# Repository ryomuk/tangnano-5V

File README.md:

# tangnano-5V
5V tolerant interface for Tang Nano 20K and 9K

This document is written mostly in Japanese. If necessary, please use a translation service such as DeepL (I recommend this) or Google.

# 概要
Tang Nanoを5V系の回路に接続するためのインターフェースです．昔のCPU用のメモリシステムやI/OをTang Nanoに実装することを主目的に作成しました。
Tang Nano 20K用と9K用の2種類があります．(私は主に20K用を使用しており，9K用はクセがあるのであまり使用実績が無いです．)

# Tang Nano 20K 版(rev.1.1a)
## 機能
- Tang Nanoの20KのGPIO(全34本)を，SN74CB3T3245(レベルシフタ搭載バススイッチ)を介して5V系(TTL, CMOS)に接続します．
- バッファではなくスイッチで行なっているため，特に信号方向を意識することなく双方向接続が可能，信号の伝達遅延は0.25ns以下です．

## 原理
- 5V→3.3VはSN74CB3T3245によって5V系から3.3V系にレベル変換されます．
- 3.3V→5Vはレベル変換は行なわれず，3.3V系の信号が出力されますが，5VTTLの閾値は1.5V，5VCMOSの閾値は2.5Vなので問題無いということのようです．

## 動作の確認状況
- 27MHzのシステムクロックが全GPIOで5V系に出力できることを確認しました．(75番ピンについては下記参照)
- 5V系→3.3V系: 5Vの入力信号に対し，出力が3.3Vになることを確認しました．
- 3.3V系→5V系: 3.3Vの入力信号に対し，出力が3.3Vになることを確認しました．
- データシートによると遅延はmax 0.25nsで，手元のオシロでは測定限界以下でした．

## Tang Nano 20Kの75番ピンについて
- Tang Nano 20K(v3921)の75番ピンは，C51(100nF)でGNDに接続されているため，そのままだと低速(数十KHz)でしか動作しません．他のピンと同様に使用するためにはC51を外す必要があります．低速動作で構わないのであれば気にしなくていいです．
- 最新の回路図v3921(Date:2023-07-11, ファイルの日付2023-11-08)ではC51がNCになっているようです。2024年3月に購入したものがC51未実装だったという情報がありました。(2024/4/15)
- R22(10K)でGNDにプルダウンされているので、外部でプルアップすると誤動作の原因になります。

### 75番ピン以外に関するメモ
TangNano20K、pin75以外にも若干癖のあるpinがあるのでメモしておきます。
- pin15～20は510RでLEDに継がっていて入力に使うとIIL=約3.0mA。
- pin52～53は2.2Kで5VとFETに継がっててIIL=約4.4mA。
- pin26は5.1KでGND、IIH=0.6mA。
- その他のほとんどのピンはだいたいIIL=0.9mA程度、IIH=0.1mA以下。

## BOM
|Reference          |Qty| Value          |Size |Memo |
|-------------------|---|----------------|-----|-----|
|C1, C2, C3, C4, C5 |5	|0.1uF	         |1608(mm)(0603(inch))| |
|J1, J2	            |2	|pin socket      |1x20 |for Tang Nano 20K|
|J3, J4             |2	|pin header      |1x20 |for 5V GPIO|
|U1, U2, U3, U4, U5 |5	|SN74CB3T3245PW  |TSSOP| |

## 画像

# 応用例
- いろいろなCPUのメモリシステム，UARTを構築した応用例です．CPUをFPGAでエミュレートするのではなく、本物のCPUを動かすことを目的にしています。
- 勉強のために作った習作なのでかなり荒削りでいろいろと不備やバグがあると思いますがご容赦下さい。
- 各CPUで共通に使用しているUARTモジュールは適当に作ったために時々不具合が見つかってバグ修正しています．旧版との互換性は確認していないので，CPUによっては旧版のままになっています．最新版は別フォルダ [applications/uart/](applications/uart/) に置いてありますので，必要であればコピーしてご使用下さい．
- ターミナルソフトの通信遅延はCPUの速度や通信速度にあわせて適宜設定して下さい。(例: 10ms/文字, 100ms/行)

## TangNanoZ80MEM [applications/TangNanoZ80MEM](applications/TangNanoZ80MEM)
- Z80用のメモリシステムとクロック，UARTです．
- 関連ブログ [Z80をオーバークロックしてみる](https://blog.goo.ne.jp/tk-80/e/6de3708450bac79c2c1cef7728d0c877)
  
## TangNanoZ80MEM-CPM [applications/TangNanoZ80MEM-CPM](applications/TangNanoZ80MEM-CPM)
- TangNanoZ80MEMにfloppy/hard diskエミュレータを追加してCP/Mを動作させる試みです．

## TangNano6809MEM [applications/TangNano6809MEM](applications/TangNano6809MEM)
- MC6809用のメモリシステムとクロック，UARTです．
- [電脳伝説さんのSBC6809](https://vintagechips.wordpress.com/2017/12/05/sbc6809%E3%83%AB%E3%83%BC%E3%82%BA%E3%82%AD%E3%83%83%E3%83%88/)のdatapackに入っているBASIC9がバイナリそのままで動きます．

## TangNano8070MEM [applications/TangNano8070MEM](applications/TangNano8070MEM)
- INS8070N(SC/MP III)用のメモリシステム，クロック，UARTです．
- [ElectrelicさんのUniversal Monitor](https://electrelic.com/electrelic/node/1317)が，UARTのハンドシェイク部分を微修正して動きました．

## TangNano8008MEM [applications/TangNano8008MEM](applications/TangNano8008MEM)
- Intel 8008用のメモリシステム，クロック，UARTです．
- [SCELBAL (SCELBI Basic)](https://www.willegal.net/scelbi/scelbal.html)が動きました．
- [VTL-4004](https://github.com/ryomuk/VTL4004)を8008用に書き直したVTL-8008が動きました

## TangNano8080MEM [applications/TangNano8080MEM](applications/TangNano8080MEM)
- Intel 8080用メモリシステム，クロック，UART，diskエミュレータです．
- Z80MEM-CPMと同じdiskイメージを使用してCP/Mが起動します．

## TangNanoDCJ11MEM [ryomuk/TangNanoDCJ11MEM](https://github.com/ryomuk/TangNanoDCJ11MEM)

- DEC DCJ11 (PDP-11の命令セットを持つCPU)のメモリシステムとUARTです。
- 詳細は別リポジトリ[TangNanoDCJ11MEM](https://github.com/ryomuk/TangNanoDCJ11MEM) にあります。

# Tang Nano 9K 版(rev.3.0)[hardware/9k](hardware/9k)
- Tang Nanoの9K用のインターフェースです．あまりメンテナナスされていません．

# その他
## UARTモジュールについて [applications/uart/](applications/uart/)
- 各応用例の通信部分はSipeedのサンプル( https://github.com/sipeed/TangNano-20K-example )をベースにして独自に書き替えたものを使っています．CPU速度と通信速度によっては不安定だったりすることがあり，時々書き直してます．旧版との互換性を全部確認するのは面倒なので最新版は別のフォルダに入れることにしました．

## 参考文献，データシート等
- [SN74CB3T3245 Data sheet](https://www.ti.com/lit/ds/symlink/sn74cb3t3245.pdf)
- [Application Note CBT-C, CB3T, and CB3Q Signal-Switch Families](https://www.ti.com/lit/an/scda008c/scda008c.pdf)
- [Logic Guide, Texas Instruments](https://www.ti.com/lit/sg/sdyu001ab/sdyu001ab.pdf)
- [ロジック・ガイド(日本語版), Texas Instruments](https://www.tij.co.jp/jp/lit/sg/jajt217/jajt217.pdf)
- [5V系・3.3V系信号レベル変換, cepstrum](https://www.cepstrum.co.jp/hobby/5v33v/5v33v.html)

## 更新履歴
- 2023/06/16: 初版公開 (Tang Nano 20K用 rev.1.1)
- 2023/06/25: 応用例にTangNanoZ80MEMを追加
- 2023/06/26: TangNanoZ80MEMのピン配置を変更．(rev1.0→rev.1.1)
- 2023/06/28: TangNanoZ80MEMの uart.vを更新．
- 2023/07/06: TangNanoZ80MEMを修正．27MHz(Vcc=5.0V), 33MHz(Vcc=6.0V)で動作．
- 2023/07/11: Tang Nano 20K用 rev.1.1→rev.1.1a (差分はシルクの修正のみ)
- 2023/07/11: Tang Nano 9K用 rev.2.0公開 (若干問題あり)
- 2023/07/15: README.md用の画像を1.1aにアップデート
- 2023/07/19: 応用例にTangNano6809MEMを追加
- 2023/07/20: tn20k5v rev1.1aの実物作成，動作確認OK．写真掲載．
- 2023/07/23: 応用例にTangNano8070MEMを追加．
- 2024/04/07: uart.vのバグ修正．(tx_ready関連)
- 2024/04/11: TangNano6809MEMに関する注意事項記載
- 2024/04/12: uart.vの最新版格納用のフォルダ applications/uart を作成
- 2024/04/13: applications/uart/uart.v 更新
- 2024/04/14: README修正(応用例に関するエクスキューズを追記)
- 2024/04/15: README修正(6809、R1の除去について, TangNano20Kのピンに関するメモ)
- 2024/04/17: TangNanoZ80MEM: top.v修正(writeのバグ, RGBLED, UART_CTRL)
- 2024/04/17: TangNanoZ80MEM: rom/rom.unimon339.v 追加
- 2024/04/19: TangNanoZ80MEM: rom/bin2v.pl修正, romファイルの余計な0フィルを削除
- 2024/04/21: Tang Nano 9K用 rev.3.0公開
- 2024/04/27: TangNanoZ80MEM: UARTの送信タイミング変更
- 2024/05/07: applications/uart/にuart.v.20240507 追加
- 2024/06/21: applications/uart/にuart.v.20240621 追加
- 2024/06/21: rx_clear, tx_sendのロジックについてREADMEに追記
- 2024/07/23: READMEを階層化
- 2024/07/23: TangNanoZ80MEM-CPM 公開
- 2024/08/05: TangNano8008MEM 公開
- 2024/08/18: TangNano8008MEM用のsoftwareにVTL-8008を追加
- 2024/08/28: TangNano8008MEMにPCB rev1.0を追加
- 2024/09/08: TangNano8080MEM 公開
- 2024/09/13: TangNano8080MEM 修正 (memory writeタイミング修正, 3MHz対応)

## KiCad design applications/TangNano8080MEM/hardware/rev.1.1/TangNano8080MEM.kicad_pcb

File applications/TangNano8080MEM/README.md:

# TangNano8080MEM

## 概要
- Intel 8080用のメモリシステム，クロック，UART，diskエミュレータです．
- Universal Monitor や CP/Mが動きます．

## PCB rev.1.1
- 回路図，ガーバーファイル等は[hardware/rev.1.1](hardware/rev.1.1/)にあります．
### BOM
|Reference          |Qty| Value          |Memo |
|-------------------|---|----------------|-----|
|C1                 |1  |2.2uF           |     |
|C2,C6              |2  |1uF             |     |
|C3,C4              |2  |10uF            |     |
|C5,C7,C8           |3  |0.1uF           |     |
|D1,D2              |2  | LED            |任意     |
|J1                 |1  | DIP-40 Socket or 20x1 Pin frame x2  |TangNano5V用|
|J2,J3              |2  |Conn_01x20      |任意(観測用)|
|PS1                |1  |MAU104          |5V→12V用DCDC,  https://akizukidenshi.com/catalog/g/g104132/ |
|PS2                |1  |TJ7660          |5V→-5V用, https://akizukidenshi.com/catalog/g/g112017/|
|R1                 |1  | 10k             |     |
|R2,R3              |2  | 1k〜100k(適宜)     | 値はLEDにあわせて任意|
|R4,R5              |2  | 47     | クロック用ダンピング抵抗|
|RN1                |1  | 4.7k x8       |データバスプルアップ     |
|RN2                |1  | 100k x4       |制御信号プルアップ       |
|U1                 |1  | MIC4427 |  クロックドライバ|
|U2                 |1  | 40pin ZIFソケット |  8080用|

- RN2は当初10KΩにしていたのですが，TangNano20Kのpin75はB616_BOOTに継がっていて，起動時にUSBを検出してくれなくなってしまうので100kΩに変更しました．[TangNano6809MEM](../TangNano6809MEM)で起きていたのと同様の問題でした．

## FPGAに実装したもの
- [TangNanoZ80MEM-CPM](../TangNanoZ80MEM-CPM/)をベースにして，2相クロック，8228相当の制御信号の変換を追加しました．

## クロックの設定
top.v で下記の1つを選択して下さい．
```
// select one of the following CLK frequency
//`define  CLK_3MHz     // 3.0MHz(333ns)
`define  CLK_2MHz   // 2.077MHz( 481ns)
//`define  CLK_1MHz   // 1.038MHz( 963ns)
//`define  CLK_500kHz // 519.2KHz(1930ns)
```

## ROMの選択
- top.v で下記の1つを選択して下さい．
```
// select one of the following 2 applications
`define USE_CPM
//`define USE_UNIMON

```
このオプションで，rom.vでincludeするファイル，UART用レジスタのビットフィールドを切り替えています．

## CP/Mの起動方法
- [TangNanoZ80-CPM](../TangNanoZ80MEM-CPM/)と同じ手順で作成したdiskイメージで起動できます．

## 動作確認状況
- 下記CPUで動作CP/Mが起動し，BASICでASCIIART.BASが完走しました．

#### Intel C8080A

#### Intel P8080A-1 (3MHz)

#### NEC uPD8080A

#### NEC uPD8080AF

#### NEC uPD8080AFC-1 (3MHz)

#### NEC uPD753(+変換基板)

#### 三菱M58710S(8080A)

#### AMD AM9080ADC(C8080A)

#### AMD AM9080ADCB

#### NS INS8080AN

#### TI TMS8080ANL

## 既知の問題
- ~~下記CPUで動作しないので原因調査中です．~~
  - ~~NS INS8080AN, TI TMS8080ANL~~
  - メモリ書き込みのタイミングを修正して解決しました．

## 参考にした先行事例，関連サイト等
- [satoshiokue/MEZ8080](https://github.com/satoshiokue/MEZ8080)
- [satoshiokue/EMUZ80-8080](https://github.com/satoshiokue/EMUZ80-8080)
- [Gazelle8087/EMUZ80-8080G](https://github.com/Gazelle8087/EMUZ80-8080G)
- [電脳伝説/SBC8080](https://vintagechips.wordpress.com/2018/06/24/sbc8080-cpu%E3%83%AB%E3%83%BC%E3%82%BA%E3%82%AD%E3%83%83%E3%83%88/)
- [Electrelic/Universal Monitor](https://electrelic.com/electrelic/node/1317)

## 更新履歴
- 2024/09/08: 初版公開
- 2024/09/13: メモリライトタイミング修正，3MHz対応

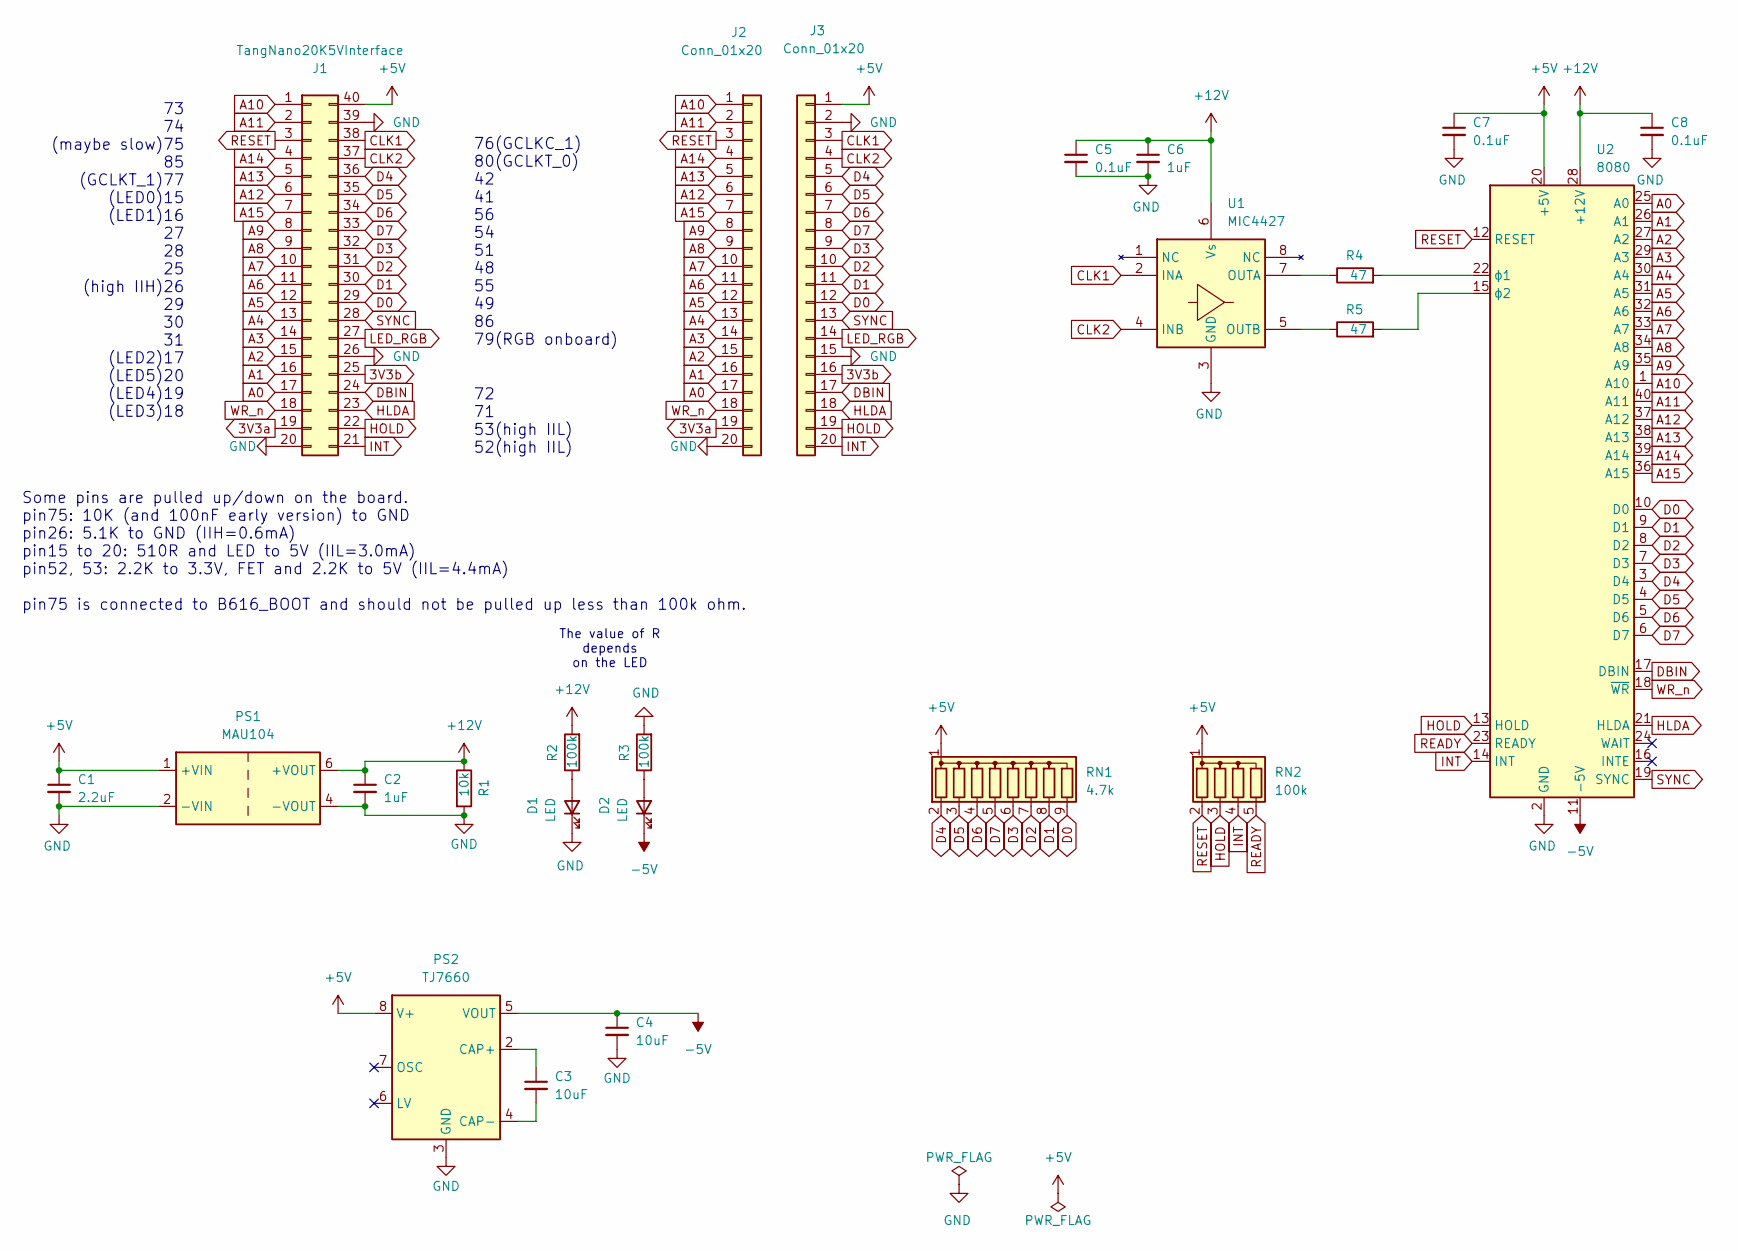
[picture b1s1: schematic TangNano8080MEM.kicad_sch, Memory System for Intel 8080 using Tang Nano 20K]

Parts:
C1: 2.2uF; C_Disc_D4.7mm_W2.5mm_P5.00mm
C2, C6: 1uF; C_Disc_D4.7mm_W2.5mm_P5.00mm
C3, C4: 10uF; C_Disc_D4.7mm_W2.5mm_P5.00mm
C5, C7, C8: 0.1uF; C_Disc_D5.0mm_W2.5mm_P2.50mm
D1, D2: LED; LED_D3.0mm
J1: TangNano20K5VInterface; DIP-40_W15.24mm_Socket
J2, J3: Conn_01x20; PinSocket_1x20_P2.54mm_Vertical
PS1: MAU104; SIP-6_without_3_5pin_for_DCDC_MAU
PS2: TJ7660; DIP-8_W7.62mm
R1: 10k; R_Axial_DIN0207_L6.3mm_D2.5mm_P7.62mm_Horizontal
R2, R3: 100k; R_Axial_DIN0207_L6.3mm_D2.5mm_P7.62mm_Horizontal
R4, R5: 47; R_Axial_DIN0207_L6.3mm_D2.5mm_P7.62mm_Horizontal
RN1: 4.7k; R_Array_SIP9
RN2: 100k; R_Array_SIP5
U1: MIC4427; DIP-8_W7.62mm
U2: 8080; DIP_Socket-40_W11.9_W12.7_W15.24_W17.78_W18.5_3M_240-1280-0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

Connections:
3V3a: J1.19, J2.19
3V3b: J1.25, J3.16
+5V: C1.1, C7.1, J1.40, J3.1, PS1.1 (+VIN), PS2.8 (V+), RN1.1 (common), RN2.1 (common), U2.20 (+5V)
+12V: C2.1, C5.1, C6.1, C8.1, PS1.6 (+VOUT), R1.1, R2.2, U1.6 (Vs), U2.28 (+12V)
-5V: C4.1, D2.1 (K), PS2.5 (VOUT), U2.11 (-5V)
A0: J1.17, J2.17, U2.25 (A0)
A1: J1.16, J2.16, U2.26 (A1)
A2: J1.15, J2.15, U2.27 (A2)
A3: J1.14, J2.14, U2.29 (A3)
A4: J1.13, J2.13, U2.30 (A4)
A5: J1.12, J2.12, U2.31 (A5)
A6: J1.11, J2.11, U2.32 (A6)
A7: J1.10, J2.10, U2.33 (A7)
A8: J1.9, J2.9, U2.34 (A8)
A9: J1.8, J2.8, U2.35 (A9)
A10: J1.1, J2.1, U2.1 (A10)
A11: J1.2, J2.2, U2.40 (A11)
A12: J1.6, J2.6, U2.37 (A12)
A13: J1.5, J2.5, U2.38 (A13)
A14: J1.4, J2.4, U2.39 (A14)
A15: J1.7, J2.7, U2.36 (A15)
CLK1: J1.38, J3.3, U1.2 (INA)
CLK2: J1.37, J3.4, U1.4 (INB)
D0: J1.29, J3.12, RN1.9 (R8), U2.10 (D0)
D1: J1.30, J3.11, RN1.8 (R7), U2.9 (D1)
D2: J1.31, J3.10, RN1.7 (R6), U2.8 (D2)
D3: J1.32, J3.9, RN1.6 (R5), U2.7 (D3)
D4: J1.36, J3.5, RN1.2 (R1), U2.3 (D4)
D5: J1.35, J3.6, RN1.3 (R2), U2.4 (D5)
D6: J1.34, J3.7, RN1.4 (R3), U2.5 (D6)
D7: J1.33, J3.8, RN1.5 (R4), U2.6 (D7)
DBIN: J1.24, J3.17, U2.17 (DBIN)
GND: C1.2, C2.2, C4.2, C5.2, C6.2, C7.2, C8.2, D1.1 (K), J1.20, J1.26, J1.39, J2.20, J3.2, J3.15, PS1.2 (-VIN), PS1.4 (-VOUT), PS2.3 (GND), R1.2, R3.2, U1.3 (GND), U2.2 (GND)
HLDA: J1.23, J3.18, U2.21 (HLDA)
HOLD: J1.22, J3.19, RN2.3 (R2), U2.13 (HOLD)
INT: J1.21, J3.20, RN2.4 (R3), U2.14 (INT)
LED_RGB: J1.27, J3.14
unnamed: D1.2 (A), R2.1
unnamed: D2.2 (A), R3.1
unnamed: C3.1, PS2.2 (CAP+)
unnamed: C3.2, PS2.4 (CAP-)
unnamed: R4.1, U1.7 (OUTA)
unnamed: R5.1, U1.5 (OUTB)
unnamed: R4.2, U2.22 (ϕ1)
unnamed: R5.2, U2.15 (ϕ2)
READY: RN2.5 (R4), U2.23 (READY)
RESET: J1.3, J2.3, RN2.2 (R1), U2.12 (RESET)
SYNC: J1.28, J3.13, U2.19 (SYNC)
WR_n: J1.18, J2.18, U2.18 (~WR)

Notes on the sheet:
72 71 53(high IIL) 52(high IIL)
73 74 (maybe slow)75 85 (GCLKT_1)77 (LED0)15 (LED1)16 27 28 25 (high IIH)26 29 30 31 (LED2)17 (LED5)20 (LED4)19 (LED3)18
76(GCLKC_1) 80(GCLKT_0) 42 41 56 54 51 48 55 49 86 79(RGB onboard)
Some pins are pulled up/down on the board. pin75: 10K (and 100nF early version) to GND pin26: 5.1K to GND (IIH=0.6mA) pin15 to 20: 510R and LED to 5V (IIL=3.0mA) pin52, 53: 2.2K to 3.3V, FET and 2.2K to 5V (IIL=4.4mA) pin75 is connected to B616_BOOT and should not be pulled up less than 100k ohm.
The value of R depends on the LED

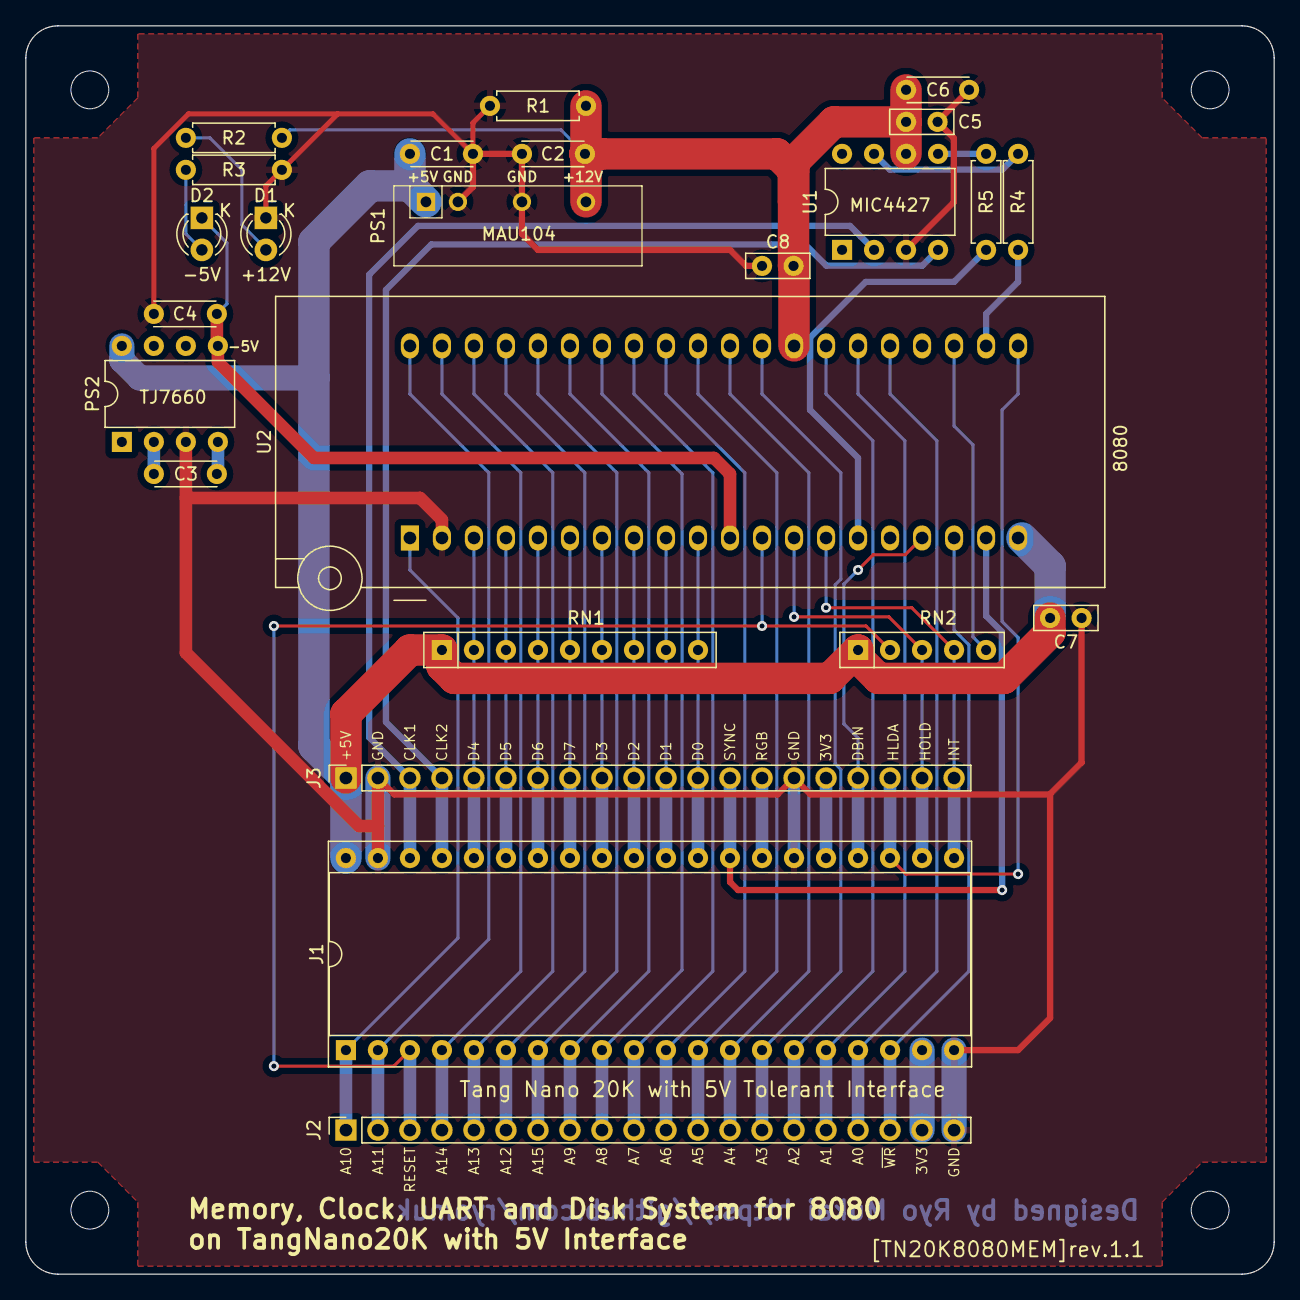
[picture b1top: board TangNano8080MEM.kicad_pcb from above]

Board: 2 copper layers, 99.1 x 99.1 mm, 24 parts (0 on the bottom side), 49 nets.

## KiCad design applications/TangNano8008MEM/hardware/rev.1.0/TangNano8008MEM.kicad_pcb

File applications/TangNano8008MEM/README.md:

# TangNano8008MEM
## 概要
- Intel 8008用のメモリシステム，クロック，UARTです．

## PCB rev.1.0

- 回路図やガーバーファイルは[hardware/rev.1.0](hardware/rev.1.0/)にあります．
- users manualには入出力はTTLレベルと書いてありますが，波形を観測したところ8008の出力はマイナス電位にもなるようでした．
  - バス(D0〜7)には外付けでクランプダイオードを回路に入れていますが，SN74CB3T3245にはクランプダイオードが内蔵されているので無くても動きます．
  - SYNC, S0〜2は1KΩの抵抗だけ入れてSN74CB3T3245内蔵のクランプダイオードに任せています．
### BOM
|Reference          |Qty| Value          |Memo |
|-------------------|---|----------------|-----|
|C1                 |1  |2.2uF           |     |
|C2                 |1  |1uF             |     |
|D1-D8              |8  |1N4148          |     |
|D9                 |1  | LED      |任意     |
|J1                 |1  | DIP-40 Socket or 20x1 Pin frame x2  |TangNano5V用|
|PS1                |1  |MAU103          |5V→9V用DCDC,  https://akizukidenshi.com/catalog/g/g112176/ |
|R1-R5              |5  | 1k             |     |
|R6                 |1  | 100k(適宜)     | 値はLEDにあわせて任意|
|RN1, RN3           |2  | 4.7k x8       |     |
|RN2                |1  | 1k x4          |     |
|U1                 |1  | 18pin ZIFソケット |  intel8008用|

## FPGAに実装したもの
- プロジェクトは[TangNano8008MEM_project](TangNano8008MEM_project)です．
- 16KBメモリ (8008のアドレス空間は14bitなのでフル実装です．)
- UART(TXバッファ付き)
- 割り込み機能
- 8008にはRESETが無いので，下記でRESET相当のことを実装しました．
  - SW1: バスにHALTを出力してSTOPさせ，INTERRUPT信号をアサートし，バスにRST0命令を挿入．(power-up時も同様)
  - SW2: INTERRUPT信号をアサートし，バスにRST0命令を挿入

## ソフトウェアについて
### VTL-8008 ([software/VTL8008](software/VTL8008))
- 以前，4004用に書いた[VTL-4004](https://github.com/ryomuk/VTL4004)を8008用に書き直してみました．仕様はVTL-4004 ver2.0と同じです．面倒なので行の編集機能が実装していません．

### echo back test ([software/echo](software/echo))
- UARTの入出力テスト用プログラムです．
- polling版と割り込み版はecho.asmの下記2行と，top.vのdefineで切り替えます．
```
echo.asm
;;; uncomment this for polling
;;  	CAL GETCH
;;  	CAL PUTCH

top.v
//`define USE_RX_INTERRUPT
```

### SCELBAL (SCELBI Basic) ([software/sc1](software/sc1))
- Twitterで[SCELBAL (SCELBI Basic)](https://www.willegal.net/scelbi/scelbal.html)なるものが存在することを教えてもらったので試してみることにしました．

#### SCELBI Basicのバイナリ作成方法等
- [ASL(The Macroassembler AS)](http://john.ccac.rwth-aachen.de:8000/as/), Perlをインストールして下さい．私はWindowsのCygwin環境で使っています．
- ASLで，radix 8とすれば良いようだったのですが，その場合に10進数をどう表記するかわからなかったので，radixは10のままで8進数にQを付けるスクリプトを書いて対処しました．その他の修正も全部スクリプト(conv.pl)で実施するようにしました．
- どうやら文字コードの8bit目が1のようで，コンソールの入出力は入出力ルーチンで対処すれば簡単だったのですが，アセンブラのプログラムの方も
```
DB "FOR"
```
を
```
DB 'F'+80H
DB 'O'+80H
DB 'R'+80H
```
のように展開する必要があるようなので変換しました．
- I/Oルーチン(CINP, CPRINT)を書く必要があったので user.asm に書きました．
  - 文字コードの8bit目が1であることへの対応．
  - どうやらCINPではecho処理も行う必要があるようでした．
- バイナリ作成手順は下記の通り．
```
cd TangNano8008MEM/software/sc1
wget https://www.willegal.net/scelbi/software/sc1.asm
cp sc1.asm sc1.asm.org
./conv.pl < sc1.asm.org > sc1.asm
make
./bin2v sc1.bin > rom.v
```
- Faster SCELBAL (2012) [sc1fast.asm](https://www.willegal.net/scelbi/software/sc1fast.asm) もconv.plで変換できました．
  - diffをとってみたらsc1.asmとの差分はほとんどありませんでした．
  - 構文解析処理を工夫して高速化しているようです．
  - mandelbrot.asmは10%ほど速くなりました．浮動小数点演算が支配項なので効果は限定的でした．

#### 実行サンプル
- お約束のASCIIART.BASを実行してみました．FOR文からGOTOで抜けるとエラーになるので微修正しました．
- 計測マクロがうまく動かず，正確な時間は測定できなかったのですが，クロッ
ク500kHzで約6時間40分で完走しました．

## ブレッドボード版

- 配線量が少なく，クロックも低速なのでブレッドボードで簡単に作れました．
 - ~~あまりに簡単に作れたので，基板を作るモチベーションが湧きません．~~
 - ブレッドボードを再利用するために基板を作りました．

## 関連情報
- [bitsavers /intel/MCS8](http://www.bitsavers.org/components/intel/MCS8/)
- [www.mars.dti.ne.jp/~mark08](http://www.mars.dti.ne.jp/~mark08/index.html) 8008に関する日本語の参考資料について網羅されています．
- [SCELBAL (SCELBI Basic)](https://www.willegal.net/scelbi/scelbal.html)
- [github.com/jim11662418/8008-SBC](https://github.com/jim11662418/8008-SBC)
- [The Macroassembler AS](http://john.ccac.rwth-aachen.de:8000/as/)

## 更新履歴
- 2024/08/05: 初版公開
- 2024/08/18: VTL-8008を追加
- 2024/08/28: KiCADファイルrev1.0をブレッドボード用からプリント基板用に変更

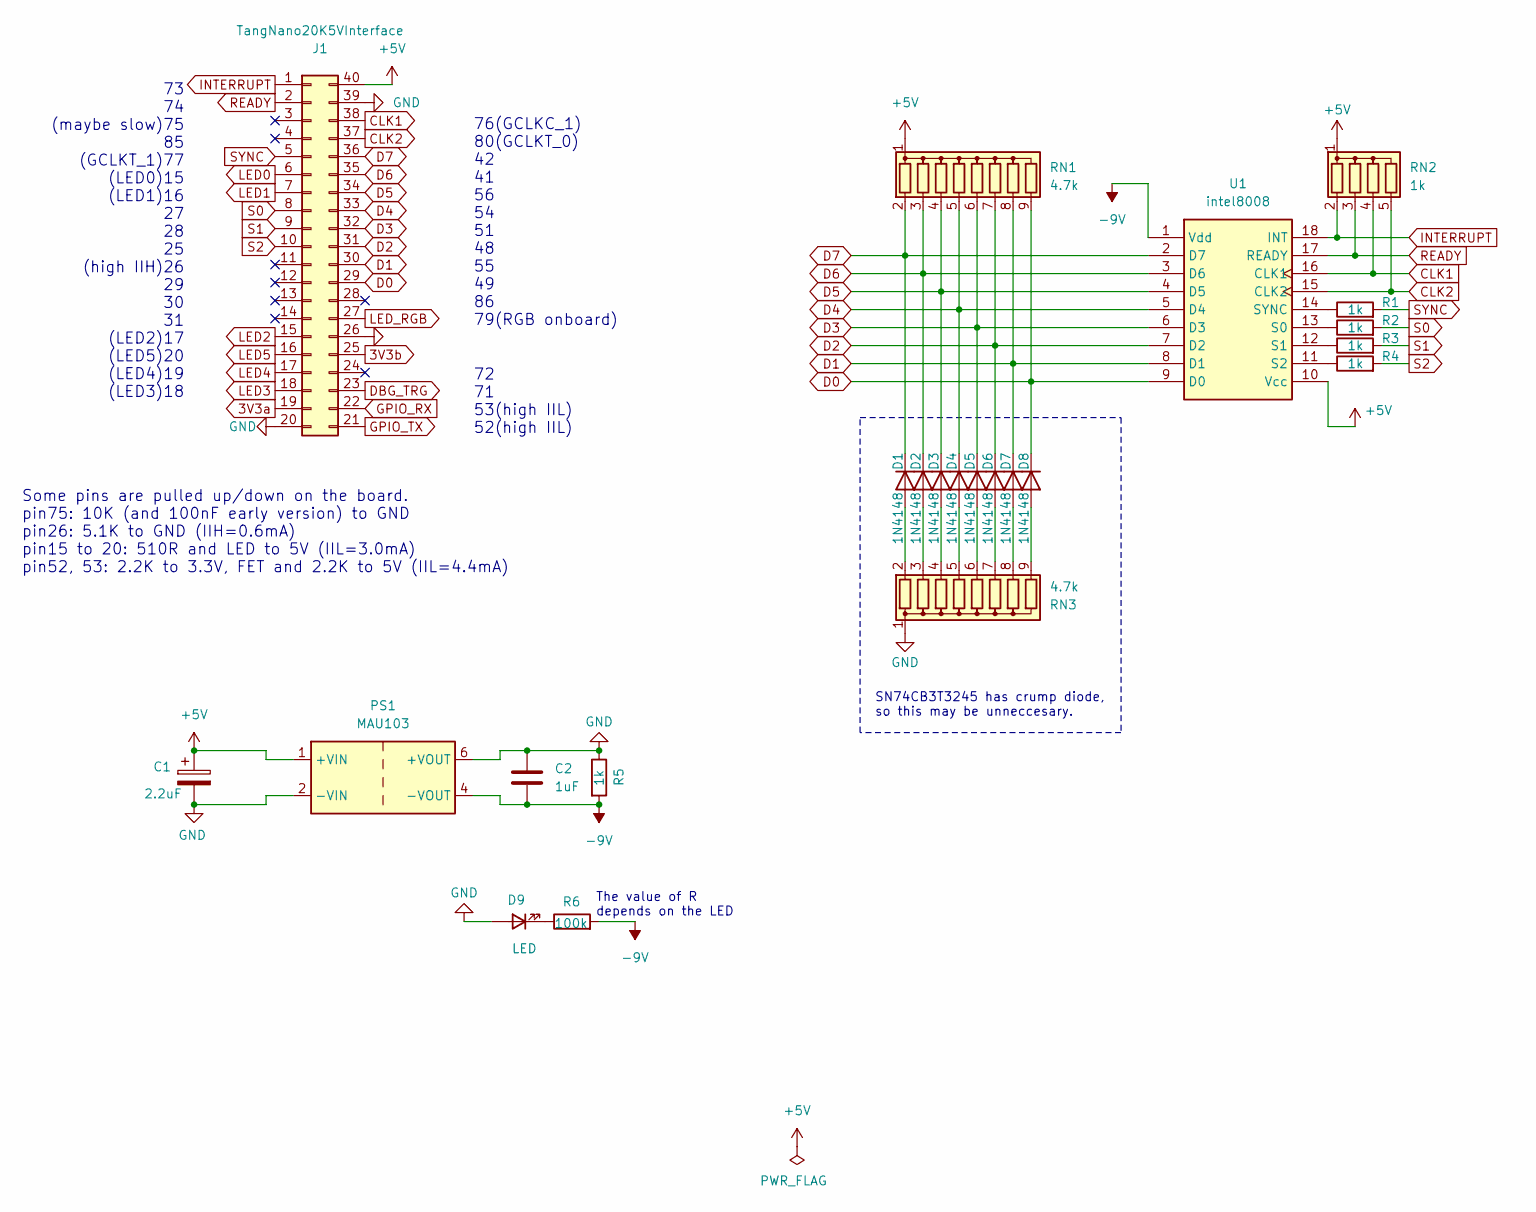
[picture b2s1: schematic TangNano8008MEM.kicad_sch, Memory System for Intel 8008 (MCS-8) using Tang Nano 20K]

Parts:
C1: 2.2uF; CP_Radial_D5.0mm_P2.00mm
C2: 1uF; C_Disc_D4.7mm_W2.5mm_P5.00mm
D1, D2, D3, D4, D5, D6, D7, D8: 1N4148; D_DO-35_SOD27_P2.54mm_Vertical_KathodeUp
D9: LED; LED_D3.0mm
J1: TangNano20K5VInterface; DIP-40_W15.24mm_Socket
PS1: MAU103; SIP-6_without_3_5pin_for_DCDC_MAU
R1, R2, R3, R4, R5: 1k; R_Axial_DIN0207_L6.3mm_D2.5mm_P7.62mm_Horizontal
R6: 100k; R_Axial_DIN0207_L6.3mm_D2.5mm_P7.62mm_Horizontal
RN1, RN3: 4.7k; R_Array_SIP9
RN2: 1k; R_Array_SIP5
U1: intel8008; DIP_Socket-18_W4.3_W5.08_W7.62_W10.16_W10.9_3M_218-3341-00-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

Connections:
3V3a: J1.19
3V3b: J1.25
+5V: C1.1, J1.40, PS1.1 (+VIN), RN1.1 (common), RN2.1 (common), U1.10 (Vcc)
-9V: C2.2, PS1.4 (-VOUT), R5.2, R6.2, U1.1 (Vdd)
CLK1: J1.38, RN2.4 (R3), U1.16 (CLK1)
CLK2: J1.37, RN2.5 (R4), U1.15 (CLK2)
D0: D8.1 (K), J1.29, RN1.9 (R8), U1.9 (D0)
D1: D7.1 (K), J1.30, RN1.8 (R7), U1.8 (D1)
D2: D6.1 (K), J1.31, RN1.7 (R6), U1.7 (D2)
D3: D5.1 (K), J1.32, RN1.6 (R5), U1.6 (D3)
D4: D4.1 (K), J1.33, RN1.5 (R4), U1.5 (D4)
D5: D3.1 (K), J1.34, RN1.4 (R3), U1.4 (D5)
D6: D2.1 (K), J1.35, RN1.3 (R2), U1.3 (D6)
D7: D1.1 (K), J1.36, RN1.2 (R1), U1.2 (D7)
DBG_TRG: J1.23
GND: C1.2, C2.1, D9.2 (A), J1.20, J1.26, J1.39, PS1.2 (-VIN), PS1.6 (+VOUT), R5.1, RN3.1 (common)
GPIO_RX: J1.22
GPIO_TX: J1.21
INTERRUPT: J1.1, RN2.2 (R1), U1.18 (INT)
LED0: J1.6
LED1: J1.7
LED2: J1.15
LED3: J1.18
LED4: J1.17
LED5: J1.16
LED_RGB: J1.27
unnamed: D1.2 (A), RN3.2 (R1)
unnamed: D2.2 (A), RN3.3 (R2)
unnamed: D3.2 (A), RN3.4 (R3)
unnamed: D4.2 (A), RN3.5 (R4)
unnamed: D5.2 (A), RN3.6 (R5)
unnamed: D6.2 (A), RN3.7 (R6)
unnamed: D7.2 (A), RN3.8 (R7)
unnamed: D8.2 (A), RN3.9 (R8)
unnamed: D9.1 (K), R6.1
unnamed: R2.1, U1.13 (S0)
unnamed: R3.1, U1.12 (S1)
unnamed: R4.1, U1.11 (S2)
unnamed: R1.1, U1.14 (SYNC)
READY: J1.2, RN2.3 (R2), U1.17 (READY)
S0: J1.8, R2.2
S1: J1.9, R3.2
S2: J1.10, R4.2
SYNC: J1.5, R1.2

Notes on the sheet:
SN74CB3T3245 has crump diode, so this may be unneccesary.
72 71 53(high IIL) 52(high IIL)
73 74 (maybe slow)75 85 (GCLKT_1)77 (LED0)15 (LED1)16 27 28 25 (high IIH)26 29 30 31 (LED2)17 (LED5)20 (LED4)19 (LED3)18
The value of R depends on the LED
76(GCLKC_1) 80(GCLKT_0) 42 41 56 54 51 48 55 49 86 79(RGB onboard)
Some pins are pulled up/down on the board. pin75: 10K (and 100nF early version) to GND pin26: 5.1K to GND (IIH=0.6mA) pin15 to 20: 510R and LED to 5V (IIL=3.0mA) pin52, 53: 2.2K to 3.3V, FET and 2.2K to 5V (IIL=4.4mA)

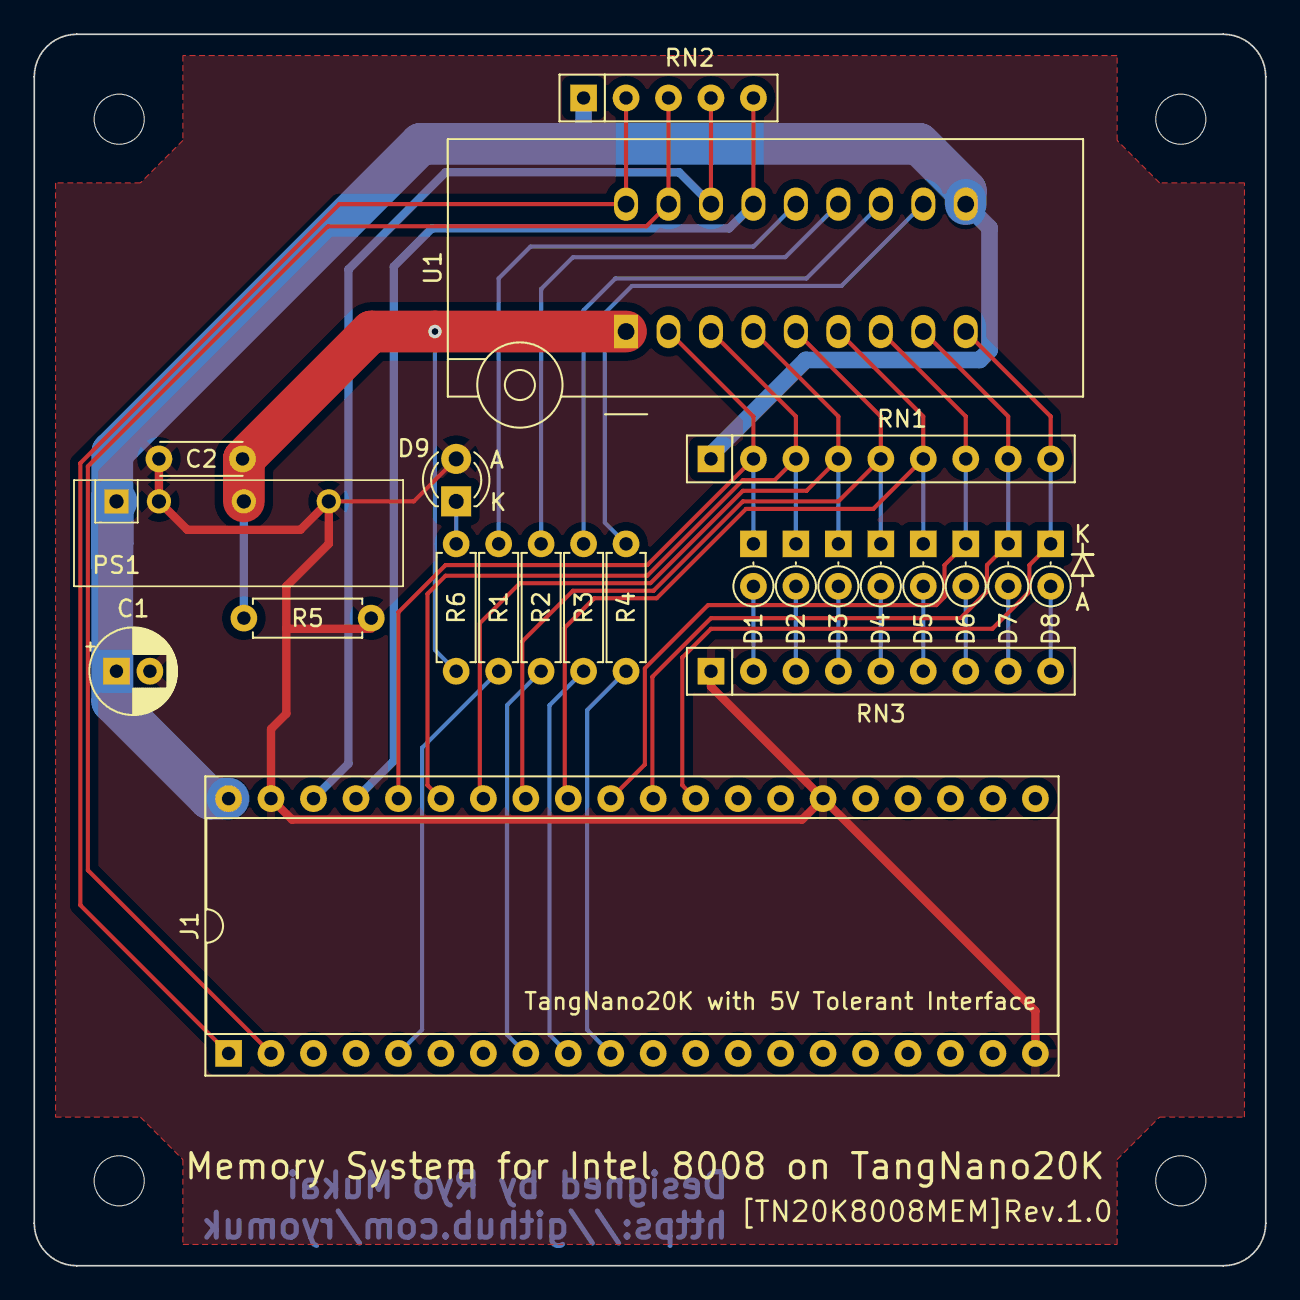
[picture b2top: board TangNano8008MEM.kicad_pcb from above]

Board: 2 copper layers, 73.7 x 73.7 mm, 23 parts (0 on the bottom side), 32 nets.

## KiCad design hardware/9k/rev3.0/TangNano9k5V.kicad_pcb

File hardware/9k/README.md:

# Tang Nano 9K 版(rev.3.0)
## rev2.0からの差分
- rev2.0(全バンクでTXS0108Eを使用)では、Pin68～75(HDMI用ピン)への入力で異常発振したり、USB接続が出来無くなったりする問題が発生していましたが、3.3Vバンクを20K版と同じ74CB3T3245に変更したところそれらの問題が解消しました。
  
## 機能
- Tang Nanoの9KのGPIO(全45本)を5V系(TTL, CMOS)に接続します．
- 信号方向を意識することなく双方向接続が可能です．
- Pin79〜86は1.8Vのバンク(BANK3)なのでTXS0108Eを用いて，1.8V←→(5V or 3.3V)の変換をします．その他のピンはCB3T3245を用いて3.3V←5V, 3.3V→3.3Vです．

## 動作の確認状況
- 27MHzのシステムクロックが全GPIOで5V系に出力できることを確認しました．
- 入力は単体試験(1ピンづつ)では期待通りの動きをしますが，入出力混在時に怪しい挙動を示しました．

### 見つかった問題点
- (pin63 & pin86) をそれ以外の全ピンに出力するというテストで出力がおかしくなることがある．おそらくBANK3(1.8V系)がなんらかの干渉をしている．
- pin68〜75は入出力とも若干歪む．

### 問題点を回避するためのガイドライン
- BANK3(1.8V系)は出力専用にする．
- HDMI用のピンは歪むので動作を確認しながら使う．

## BOM
|Reference            |Qty| Value          |Size |Memo |
|---------------------|---|----------------|-----|-----|
|C3,C4,C5,C6,C7,C8,C9 |7  |0.1uF	   |1608(mm)(0603(inch))|C1,C2は無し |
|J1                   |1  |pin header      |1x3 |BANK3 HI側の電圧選択用|
|J2,J3                |2  |pin socket      |1x24 |for TangNano9K|
|J4,J5                |2  |pin header      |1x24 |for 5V GPIO|
|PS1                  |1  |TLV71318        |SOT23-5| 1.8Vレギュレータ|
|U1                   |1  |TXS0108EPW      |TSSOP| |
|U2,U3,U4,U5,U6       |5  |SN74CB3T3245PW  |TSSOP| |

- C1,C2は.1.8Vレギュレータ用でしたが不要なので消した後にアノテーションし直すのを忘れて欠番になっています．

## 画像

## 応用例
## TangNanoZ80MEM_9K [applications/9K/TangNanoZ80MEM_9K](../../applications/9K/TangNanoZ80MEM_9K)

- 9K用インターフェースの動作確認用にブレッドボードで組んでみました．
- ~~とりあえず4.5MHzならたいていのピン配置で動きました．今のところ13.5MHzが限界．20K版ほど高速には動作しませんでした．~~
- ~~HDMIのコンデンサを外したら余計に動作しなくなったり，ピンアサインを変えるだけで動作しなくなったりするのでどこかにタイミング的な問題がありそうです．~~
- ~~MREQ_nはHDMIピンに継げた方が安定するので，MREQ_nでアドレスをラッチしているあたりが怪しそう．~~
- メモリライトのタイミングをWR_nではなくCLKでトリガーするようにしたら27MHzでも動くようになりました。ただし、HDMI端子のコンデンサ除去必須です。

## 更新履歴
- 2023/7/11: Tang Nano 9K用 rev.2.0公開 (若干問題あり)
- 2024/4/21: Tang Nano 9K用 rev.3.0公開

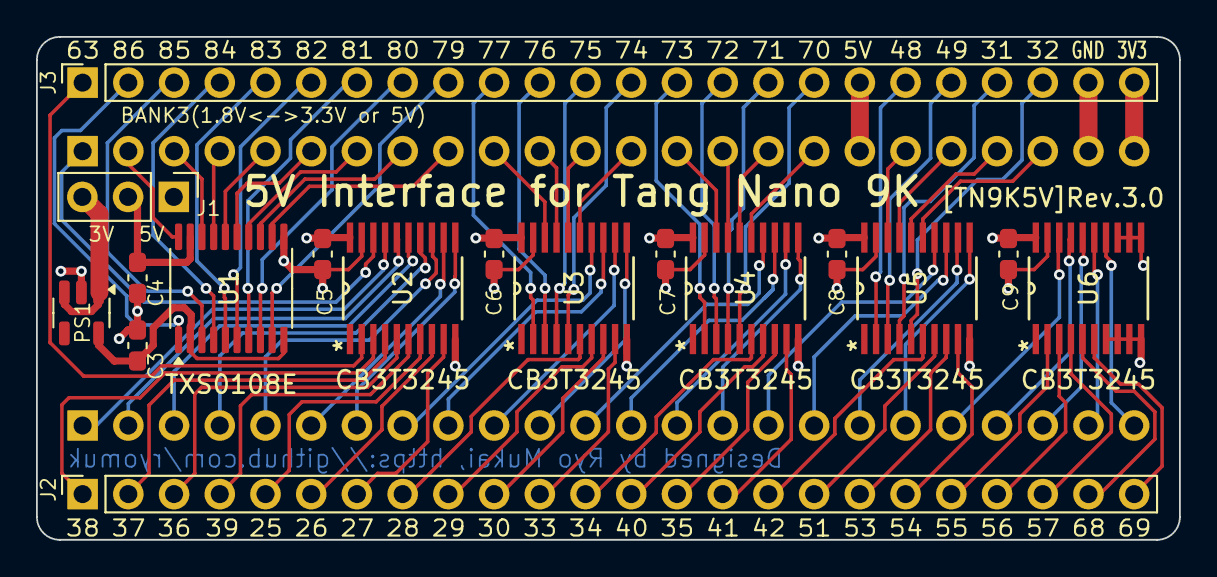
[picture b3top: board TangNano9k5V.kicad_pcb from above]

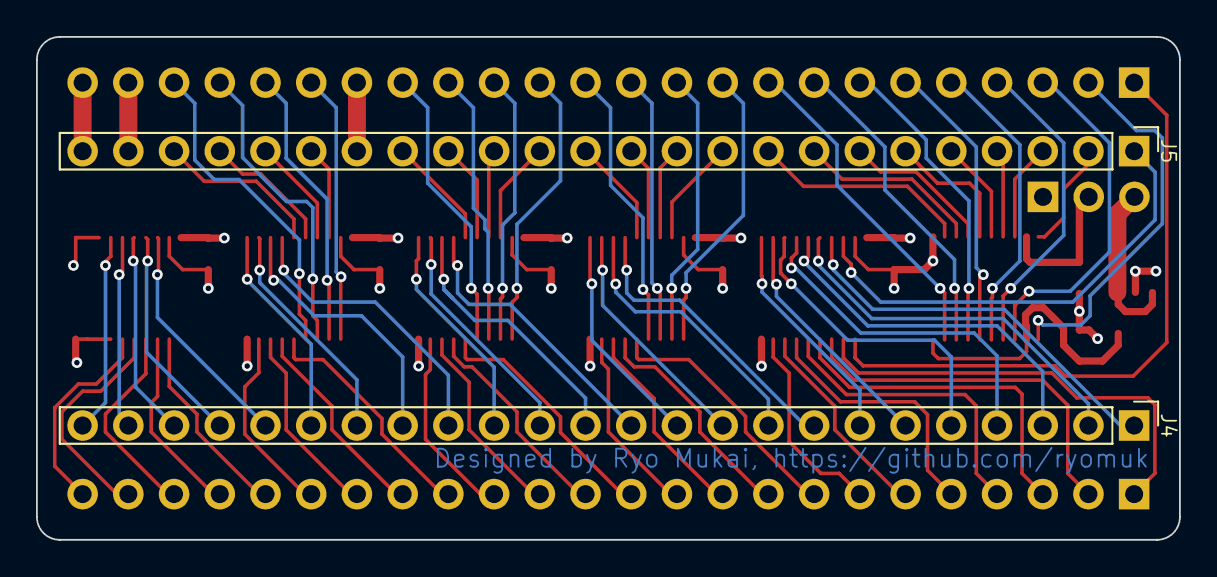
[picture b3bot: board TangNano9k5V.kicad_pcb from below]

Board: 4 copper layers, 63.5 x 27.9 mm, 19 parts (2 on the bottom side), 95 nets.

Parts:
C3, C4, C5, C6, C7, C8, C9: 0.1uF; C_0603_1608Metric_Pad1.08x0.95mm_HandSolder
J1: VCCB; PinHeader_1x03_P2.54mm_Vertical
J2, J3: Conn_01x24; PinSocket_1x24_P2.54mm_Vertical
J4, J5: Conn_01x24; PinHeader_1x24_P2.54mm_Vertical
PS1: TLV71318_SOT23-5; SOT-23-5
U1: TXS0108E; TSSOP-20_4.4x6.5mm_P0.65mm
U2, U3, U4, U5, U6: CB3T3245; PW20

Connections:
+1V8: C3.1, PS1.5 (OUT), U1.2 (VCCA), U1.10 (OE)
+3.3V: C5.1, C6.1, C7.1, C8.1, C9.1, J1.3, J3.24, J5.24, PS1.1 (IN), PS1.3 (EN), U2.20 (VCC), U3.20 (VCC), U4.20 (VCC), U5.20 (VCC), U6.20 (VCC)
+5V: J1.1, J3.18, J5.18
GND: C3.2, C4.2, C5.2, C6.2, C7.2, C8.2, C9.2, J3.23, J5.23, PS1.2 (GND), U1.11 (GND), U2.10 (GND), U2.19 (*OE), U3.10 (GND), U3.19 (*OE), U4.10 (GND), U4.19 (*OE), U5.10 (GND), U5.19 (*OE), U6.7 (A6), U6.8 (A7), U6.9 (A8), U6.10 (GND), U6.11 (B8), U6.12 (B7), U6.13 (B6), U6.19 (*OE)
unnamed: C4.1, J1.2, U1.19 (VCCB)
PIN25: J2.5, U2.7 (A6)
PIN25_H: J4.5, U2.13 (B6)
PIN26: J2.6, U2.8 (A7)
PIN26_H: J4.6, U2.12 (B7)
PIN27: J2.7, U2.9 (A8)
PIN27_H: J4.7, U2.11 (B8)
PIN28: J2.8, U3.6 (A5)
PIN28_H: J4.8, U3.14 (B5)
PIN29: J2.9, U3.7 (A6)
PIN29_H: J4.9, U3.13 (B6)
PIN30: J2.10, U3.8 (A7)
PIN30_H: J4.10, U3.12 (B7)
PIN31: J3.21, U5.4 (A3)
PIN31_H: J5.21, U5.16 (B3)
PIN32: J3.22, U5.5 (A4)
PIN32_H: J5.22, U5.15 (B4)
PIN33: J2.11, U3.9 (A8)
PIN33_H: J4.11, U3.11 (B8)
PIN34: J2.12, U4.6 (A5)
PIN34_H: J4.12, U4.14 (B5)
PIN35: J2.14, U4.8 (A7)
PIN35_H: J4.14, U4.12 (B7)
PIN36: J2.3, U2.5 (A4)
PIN36_H: J4.3, U2.15 (B4)
PIN37: J2.2, U2.4 (A3)
PIN37_H: J4.2, U2.16 (B3)
PIN38: J2.1, U2.3 (A2)
PIN38_H: J4.1, U2.17 (B2)
PIN39: J2.4, U2.6 (A5)
PIN39_H: J4.4, U2.14 (B5)
PIN40: J2.13, U4.7 (A6)
PIN40_H: J4.13, U4.13 (B6)
PIN41: J2.15, U4.9 (A8)
PIN41_H: J4.15, U4.11 (B8)
PIN42: J2.16, U5.6 (A5)
PIN42_H: J4.16, U5.14 (B5)
PIN48: J3.19, U5.2 (A1)
PIN48_H: J5.19, U5.18 (B1)
PIN49: J3.20, U5.3 (A2)
PIN49_H: J5.20, U5.17 (B2)
PIN51: J2.17, U5.7 (A6)
PIN51_H: J4.17, U5.13 (B6)
PIN53: J2.18, U5.8 (A7)
PIN53_H: J4.18, U5.12 (B7)
PIN54: J2.19, U5.9 (A8)
PIN54_H: J4.19, U5.11 (B8)
PIN55: J2.20, U6.2 (A1)
PIN55_H: J4.20, U6.18 (B1)
PIN56: J2.21, U6.3 (A2)
PIN56_H: J4.21, U6.17 (B2)
PIN57: J2.22, U6.4 (A3)
PIN57_H: J4.22, U6.16 (B3)
PIN63: J3.1, U2.2 (A1)
PIN63_H: J5.1, U2.18 (B1)
PIN68: J2.23, U6.5 (A4)
PIN68_H: J4.23, U6.15 (B4)
PIN69: J2.24, U6.6 (A5)
PIN69_H: J4.24, U6.14 (B5)
PIN70: J3.17, U4.5 (A4)
PIN70_H: J5.17, U4.15 (B4)
PIN71: J3.16, U4.4 (A3)
PIN71_H: J5.16, U4.16 (B3)
PIN72: J3.15, U4.3 (A2)
PIN72_H: J5.15, U4.17 (B2)
PIN73: J3.14, U4.2 (A1)
PIN73_H: J5.14, U4.18 (B1)
PIN74: J3.13, U3.5 (A4)
PIN74_H: J5.13, U3.15 (B4)
PIN75: J3.12, U3.4 (A3)
PIN75_H: J5.12, U3.16 (B3)
PIN76: J3.11, U3.3 (A2)
PIN76_H: J5.11, U3.17 (B2)
PIN77: J3.10, U3.2 (A1)
PIN77_H: J5.10, U3.18 (B1)
PIN79: J3.9, U1.9 (A8)
PIN79_H: J5.9, U1.12 (B8)
PIN80: J3.8, U1.8 (A7)
PIN80_H: J5.8, U1.13 (B7)
PIN81: J3.7, U1.7 (A6)
PIN81_H: J5.7, U1.14 (B6)
PIN82: J3.6, U1.6 (A5)
PIN82_H: J5.6, U1.15 (B5)
PIN83: J3.5, U1.5 (A4)
PIN83_H: J5.5, U1.16 (B4)
PIN84: J3.4, U1.4 (A3)
PIN84_H: J5.4, U1.17 (B3)
PIN85: J3.3, U1.3 (A2)
PIN85_H: J5.3, U1.18 (B2)
PIN86: J3.2, U1.1 (A1)
PIN86_H: J5.2, U1.20 (B1)

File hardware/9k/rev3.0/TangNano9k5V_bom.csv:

Reference,Value,Datasheet,Footprint,Qty,DNP
"C3,C4,C5,C6,C7,C8,C9",0.1uF,~,000_MyFootprint:C_0603_1608Metric_Pad1.08x0.95mm_HandSolder,7,
J1,VCCB,~,000_MyFootprint:PinHeader_1x03_P2.54mm_Vertical,1,
"J2,J3,J4,J5",Conn_01x24,~,,4,
PS1,TLV71318_SOT23-5,http://www.ti.com/lit/ds/symlink/tlv713.pdf,Package_TO_SOT_SMD:SOT-23-5,1,
U1,TXS0108EPW,www.ti.com/lit/ds/symlink/txs0108e.pdf,Package_SO:TSSOP-20_4.4x6.5mm_P0.65mm,1,
"U2,U3,U4,U5,U6",SN74CB3T3245PW,SN74CB3T3245PW,000_MyFootprint:PW20,5,

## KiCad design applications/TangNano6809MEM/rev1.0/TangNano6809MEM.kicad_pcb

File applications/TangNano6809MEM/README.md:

# TangNano6809MEM
- MC6809用のメモリシステムとクロック，UARTです．
- [電脳伝説さんのSBC6809](https://vintagechips.wordpress.com/2017/12/05/sbc6809%E3%83%AB%E3%83%BC%E3%82%BA%E3%82%AD%E3%83%83%E3%83%88/)のdatapackに入っているBASIC9がバイナリそのままで動きます．

BASIC9起動画面

ASCIIART.BAS実行結果 (外部クロック6MHz)

## 注意事項
- PC接続時にUSB経由の通信が確立しない問題があることがわかりました．
- ~~入力に使用しているピンのどれかがUSB-JTAGの初期化用の信号と競合しているのが原因な気がしますが特定できませんでした．~~
- ~~下記のようにVCCのラインを切断して，PCと接続後に6809のVCCを継げるという手順が必要です．~~  ~~images/6809_vcc.jpg~~
- RESET_n(pin75)のプルアップ抵抗(R1)が原因でした。pin75は内部で10KでプルダウンされていてB616_BOOTに継がっており、それと競合していました。
- R1を外すことにより上記問題は解決します。

## 更新履歴
- 2023/07/19: 応用例にTangNano6809MEMを追加
- 2024/04/11: TangNano6809MEMに関する注意事項記載
- 2024/04/15: README修正(6809、R1の除去について, TangNano20Kのピンに関するメモ)

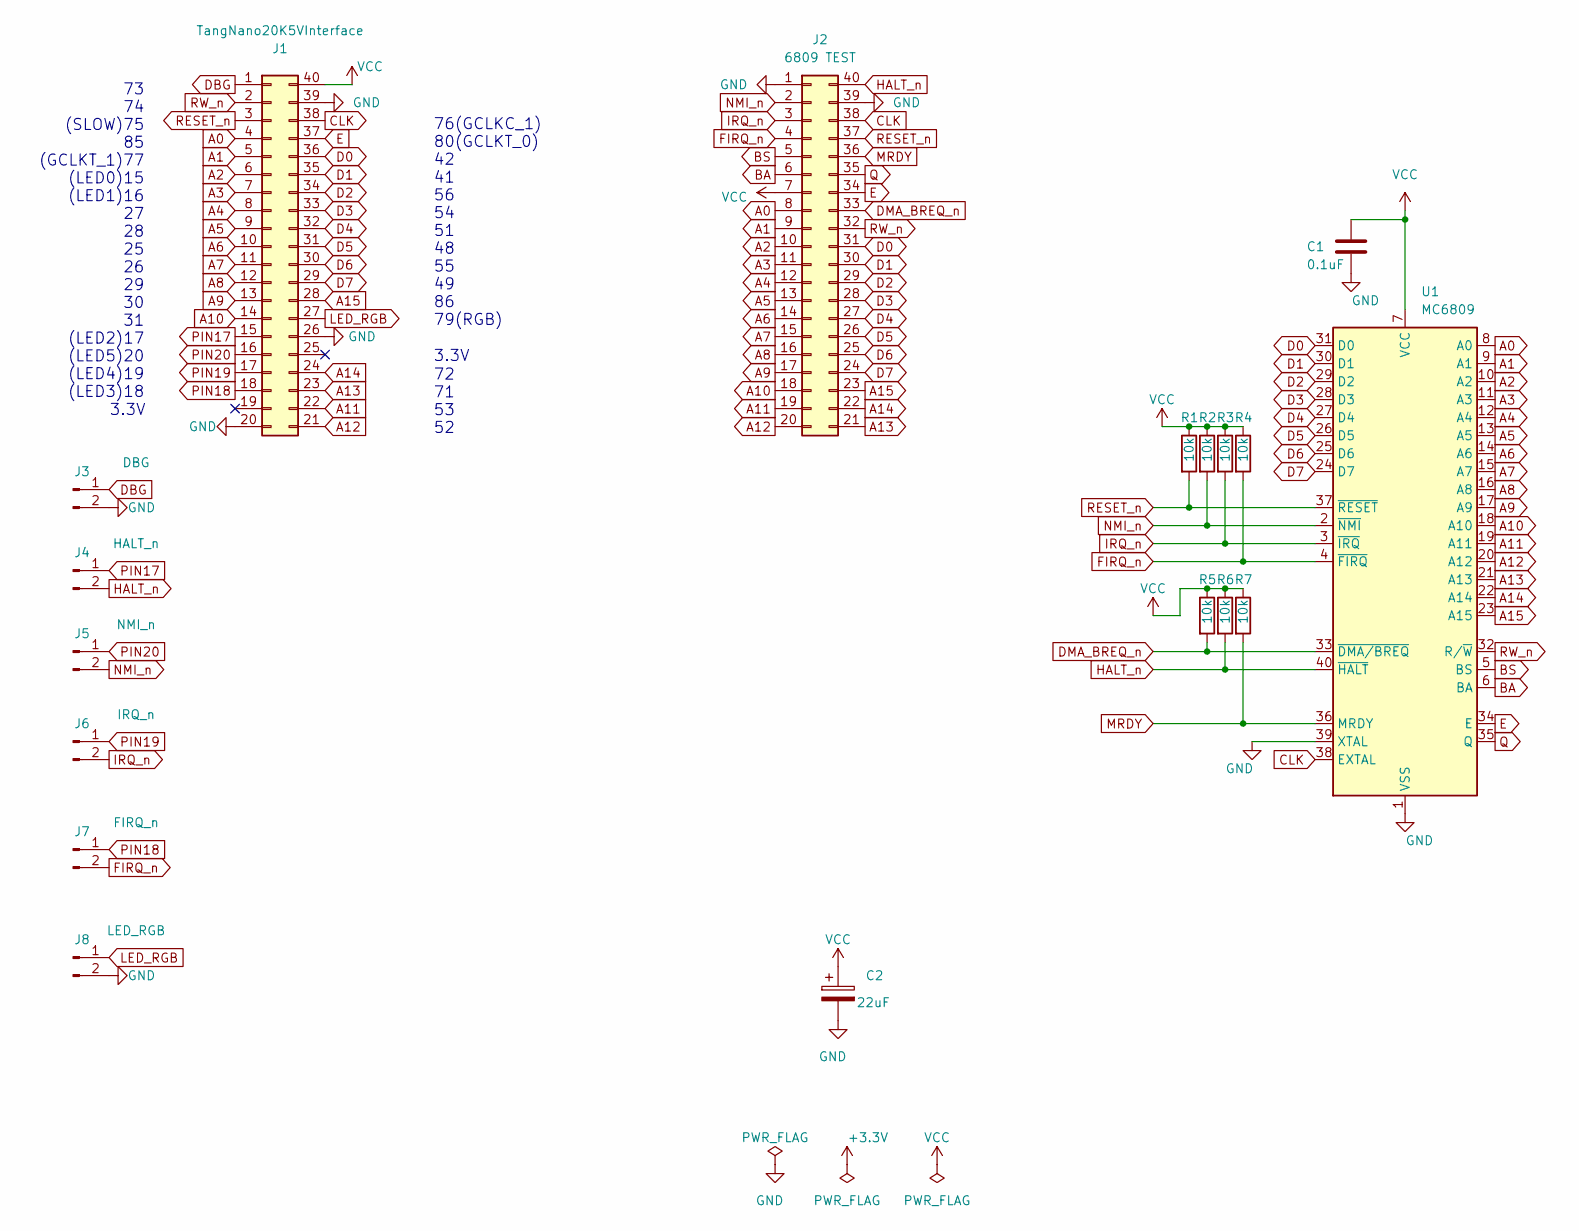
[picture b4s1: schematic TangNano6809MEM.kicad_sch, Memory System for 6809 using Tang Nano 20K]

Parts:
C1: 0.1uF; C_Disc_D4.3mm_W1.9mm_P5.00mm
C2: 22uF; CP_Radial_D4.0mm_P1.50mm
J1: TangNano20K5VInterface; DIP-40_W15.24mm_Socket
J2: 6809 TEST; DIP-40_W20.32mm800mil_Socket
J3: DBG; PinHeader_1x02_P2.54mm_Vertical
J4: HALT_n; PinHeader_1x02_P2.54mm_Vertical
J5: NMI_n; PinHeader_1x02_P2.54mm_Vertical
J6: IRQ_n; PinHeader_1x02_P2.54mm_Vertical
J7: FIRQ_n; PinHeader_1x02_P2.54mm_Vertical
J8: LED_RGB; PinHeader_1x02_P2.54mm_Vertical
R1, R2, R3, R4, R5, R6, R7: 10k; R_Axial_DIN0207_L6.3mm_D2.5mm_P7.62mm_Horizontal
U1: MC6809; DIP-40_W15.24mm

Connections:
A0: J1.4, J2.8, U1.8 (A0)
A1: J1.5, J2.9, U1.9 (A1)
A2: J1.6, J2.10, U1.10 (A2)
A3: J1.7, J2.11, U1.11 (A3)
A4: J1.8, J2.12, U1.12 (A4)
A5: J1.9, J2.13, U1.13 (A5)
A6: J1.10, J2.14, U1.14 (A6)
A7: J1.11, J2.15, U1.15 (A7)
A8: J1.12, J2.16, U1.16 (A8)
A9: J1.13, J2.17, U1.17 (A9)
A10: J1.14, J2.18, U1.18 (A10)
A11: J1.22, J2.19, U1.19 (A11)
A12: J1.21, J2.20, U1.20 (A12)
A13: J1.23, J2.21, U1.21 (A13)
A14: J1.24, J2.22, U1.22 (A14)
A15: J1.28, J2.23, U1.23 (A15)
BA: J2.6, U1.6 (BA)
BS: J2.5, U1.5 (BS)
CLK: J1.38, J2.38, U1.38 (EXTAL)
D0: J1.36, J2.31, U1.31 (D0)
D1: J1.35, J2.30, U1.30 (D1)
D2: J1.34, J2.29, U1.29 (D2)
D3: J1.33, J2.28, U1.28 (D3)
D4: J1.32, J2.27, U1.27 (D4)
D5: J1.31, J2.26, U1.26 (D5)
D6: J1.30, J2.25, U1.25 (D6)
D7: J1.29, J2.24, U1.24 (D7)
DBG: J1.1, J3.1
DMA_BREQ_n: J2.33, R5.2, U1.33 (~DMA/BREQ)
E: J1.37, J2.34, U1.34 (E)
FIRQ_n: J2.4, J7.2, R4.2, U1.4 (~FIRQ)
GND: C1.2, C2.2, J1.20, J1.26, J1.39, J2.1, J2.39, J3.2, J8.2, U1.1 (VSS), U1.39 (XTAL)
HALT_n: J2.40, J4.2, R6.2, U1.40 (~HALT)
IRQ_n: J2.3, J6.2, R3.2, U1.3 (~IRQ)
LED_RGB: J1.27, J8.1
MRDY: J2.36, R7.2, U1.36 (MRDY)
NMI_n: J2.2, J5.2, R2.2, U1.2 (~NMI)
PIN17: J1.15, J4.1
PIN18: J1.18, J7.1
PIN19: J1.17, J6.1
PIN20: J1.16, J5.1
Q: J2.35, U1.35 (Q)
RESET_n: J1.3, J2.37, R1.2, U1.37 (~RESET)
RW_n: J1.2, J2.32, U1.32 (R/~W)
VCC: C1.1, C2.1, J1.40, J2.7, R1.1, R2.1, R3.1, R4.1, R5.1, R6.1, R7.1, U1.7 (VCC)

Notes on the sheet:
72 71 53 52
73 74 (SLOW)75 85 (GCLKT_1)77 (LED0)15 (LED1)16 27 28 25 26 29 30 31 (LED2)17 (LED5)20 (LED4)19 (LED3)18
76(GCLKC_1) 80(GCLKT_0) 42 41 56 54 51 48 55 49 86 79(RGB)
3.3V
